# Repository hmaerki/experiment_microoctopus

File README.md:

# HIL (Hardware in the Loop) testinfrastructure

**This repo has to be moved to https://github.com/octoprobe**

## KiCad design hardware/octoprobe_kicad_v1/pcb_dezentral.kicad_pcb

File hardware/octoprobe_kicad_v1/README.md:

# Octoprobe v1

## Terms
`opto-pico`: The raspberry pi pico which controls the tentacle

## Goals to be achieved with this board

### No button update of opto-pico

Setup
* 1 tentacle with opto-pico

Result
* Tune TP6 cap for BOOTSEL-mode

### Automate opto-pico

Setup
* 1 RHS USB Hub (2 opto-pico)
* Two tentacles

Result
* Automatically detect tentacles on USB hub (pyusb, pyudev)
* Automatically update micropython on opto-pico
* Assignments of opto-pico serial to USB hub port identifier

### Update DUT

Setup
* 1 RHS USB Hub (2 opto-pico, 1 DUT-pico, 1 DUT-pyboard)
* Tentacle A: Raspberry Pi Pico
  * update pico using `picotool`
* Tentacle B: pyboard
  * update pybard using `dfu-util`

Result
* Automatically update FW on tentacle A
  * Optorelays on boot button
  * install micropython and testcode
* Automatically update FW on tentacle B
  * Optorelays on boot button
  * install micropython and testcode

## Kicad

### Multiconnector

GND, GND, 3V3, 5V, RELAYS0..5: 10 pins

* Testpoint
* 2 Muffe
* 2 Lötauge

A) Kicad repeat
B) Footprint mit Testpoint, 2 Muffe, 2 Lötauge
C) Footprint mit 10 Testpoint, 10x2 Muffe, 10x2 Lötauge
D) Parametrierbarer Python Code. Symbol Name ist vordefiniert.
E) Symbol `Conn_01x10_Pin`
   Parametrierbarer Python Code, welcher die entsprechenden Pins benennt.

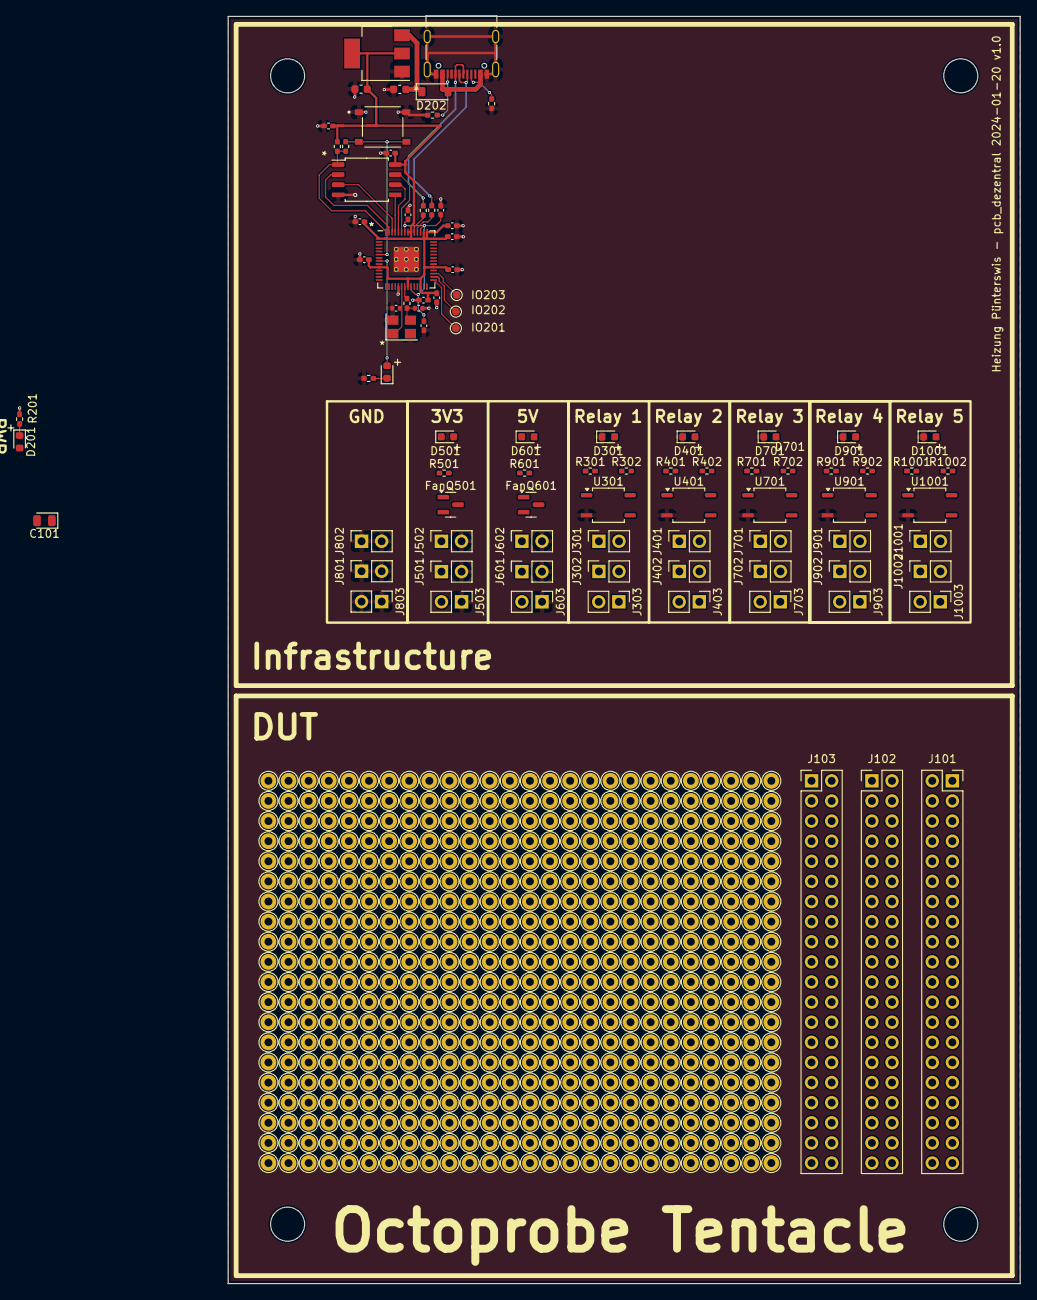
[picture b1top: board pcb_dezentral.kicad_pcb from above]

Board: 2 copper layers, 100.0 x 160.0 mm, 100 parts (0 on the bottom side), 58 nets.

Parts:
C101: 100n 50V; D_0805_2012Metric
C201, C202: 10u; C_0603_1608Metric
C203, C204, C207, C208, C209, C212, C213, C214, C215, C216: 100n; C_0402_1005Metric_Pad0.74x0.62mm_HandSolder
C205, C206: 1u; C_0402_1005Metric_Pad0.74x0.62mm_HandSolder
C210, C211: 30p; C_0402_1005Metric
D101, D301, D401, D701, D901, D1001: LED WHITE; LED_0603_1608Metric
D201: LED GREEN; LED_0603_1608Metric
D202: B5819W SL; D_SOD-123
D501, D601: RED; LED_0603_1608Metric
FanQ501, FanQ601: NMOS; SOT-23
IO201, IO202, IO203: TestPoint; TestPoint_Pad_D1.0mm
J101: Conn_01x20; PinSocket_2x20_P2.54mm_Vertical-stackable
J102: Conn_01x20; PinSocket_2x20_P2.54mm_Vertical-mirrored
J103: Conn_01x20; PinSocket_2x20_P2.54mm_Vertical-mirrored-bare
J201: USB_C_Receptacle_USB2.0; USB_C_Receptacle_Palconn_UTC16-G
J301, J302, J401, J402, J501, J502, J601, J602, J701, J702, J801, J802, J901, J902, J1001, J1002: Conn_01x02_Socket; PinSocket_1x02_P2.54mm_Vertical
J303, J403, J503, J603, J703, J803, J903, J1003: Conn_01x02_Pin; PinHeader_1x02_P2.54mm_Vertical
R101, R201, R501, R601: 470R; R_0402_1005Metric_Pad0.72x0.64mm_HandSolder
R202, R203: 27R; R_0402_1005Metric_Pad0.72x0.64mm_HandSolder
R204, R205: 5.1K; R_0402_1005Metric_Pad0.72x0.64mm_HandSolder
R206: 1K; R_0402_1005Metric_Pad0.72x0.64mm_HandSolder
R207, R302, R402, R702, R902, R1002: 10K; R_0402_1005Metric_Pad0.72x0.64mm_HandSolder
R208, R301, R401, R701, R901, R1001: 1k; R_0402_1005Metric_Pad0.72x0.64mm_HandSolder
SW201: SW_MEC_5E; SW_TS-1187A-B-A-B
U201: RP2040; RP2040-QFN-56
U202: AMS1117-3.3; SOT-223-3_TabPin2
U203: W25Q128JVS; SOIC-8_5.23x5.23mm_P1.27mm
U301, U401, U701, U901, U1001: GAQY221S; SOP-4_3.8x4.1mm_P2.54mm
UR101, UR801: GND; opctoprobe_relay
UR301: Relay 1; opctoprobe_relay
UR401: Relay 2; opctoprobe_relay
UR501: 3V3; opctoprobe_relay
UR601: 5V; opctoprobe_relay
UR701: Relay 3; opctoprobe_relay
UR901: Relay 4; opctoprobe_relay
UR1001: Relay 5; opctoprobe_relay
Y201: Crystal_GND24_Small; Crystal_SMD_3225-4Pin_3.2x2.5mm

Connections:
+1V1: C203.1, C204.1, C205.1, U201.23 (DVDD), U201.45 (VREG-VOUT), U201.50 (DVDD)
+3V3: C101.2, C202.1, C206.1, C207.1, C208.1, C209.1, C212.1, C213.1, C214.1, C215.1, C216.1, D201.2 (A), FanQ501.3 (D), R207.1, U201.1 (IOVDD), U201.10 (IOVDD), U201.22 (IOVDD), U201.26 (RUN), U201.33 (IOVDD), U201.42 (IOVDD), U201.43 (ADC-AVDD), U201.44 (VREG-VIN), U201.48 (USB-VDD), U201.49 (IOVDD), U202.2 (VO), U203.8 (VCC)
+5V: C201.1, D202.1 (K), FanQ601.3 (D), U202.3 (VI)
/Relay 4/RELAY_IN: R901.2, R902.1
/Relay 5/RELAY_IN: R1001.2, R1002.1
/cpu/QSPI_SCLK: U201.52 (QSPI-SCLK), U203.6 (CLK)
/cpu/QSPI_SD0: U201.53 (QSPI-SD0), U203.5 (DI(IO0))
/cpu/QSPI_SD1: U201.55 (QSPI-SD1), U203.2 (DO(IO1))
/cpu/QSPI_SD2: U201.54 (QSPI-SD2), U203.3 (IO2)
/cpu/QSPI_SD3: U201.51 (QSPI-SD3), U203.7 (IO3)
/cpu/QSPI_SS: R206.2, R207.2, U201.56 (QSPI-SS-N), U203.1 (~CS)
/cpu/USB_D+: J201.A6 (D+), J201.B6 (D+), R202.1
/cpu/USB_D-: J201.A7 (D-), J201.B7 (D-), R203.1
/cpu/XIN: C210.1, U201.20 (XIN), Y201.1
/cpu/XOUT: R208.1, U201.21 (XOUT)
DUT_3V3: FanQ501.2 (S), J501.1, J502.1, J503.2, R501.2
DUT_5V: FanQ601.2 (S), J601.1, J602.1, J603.2, R601.2
GND: C101.1, C201.2, C202.2, C203.2, C204.2, C205.2, C206.2, C207.2, C208.2, C209.2, C210.2, C211.2, C212.2, C213.2, C214.2, C215.2, C216.2, D301.1 (K), D401.1 (K), D701.1 (K), D901.1 (K), D1001.1 (K), J201.A1 (GND), J201.A12 (GND), J201.B1 (GND), J201.B12 (GND), J201.S1 (SHIELD), J501.2, J502.2, J503.1, J601.2, J602.2, J603.1, J801.1, J801.2, J802.1, J802.2, J803.1, J803.2, R101.1, R201.1, R204.2, R205.2, SW201.1, SW201.2, U201.19 (TESTEN), U201.57 (GND), U202.1 (GND), U203.4 (GND), U301.2, U401.2, U701.2, U901.2, U1001.2, Y201.2, Y201.4
unnamed: C211.1, R208.2, Y201.3
unnamed: D101.1 (K), R101.2
unnamed: D201.1 (K), R201.2
unnamed: D202.2 (A), J201.A4 (VBUS), J201.A9 (VBUS), J201.B4 (VBUS), J201.B9 (VBUS)
unnamed: D301.2 (A), R301.1
unnamed: D401.2 (A), R401.1
unnamed: D501.2 (A), FanQ501.1 (G)
unnamed: D501.1 (K), R501.1
unnamed: D601.2 (A), FanQ601.1 (G)
unnamed: D601.1 (K), R601.1
unnamed: D701.2 (A), R701.1
unnamed: D901.2 (A), R901.1
unnamed: D1001.2 (A), R1001.1
unnamed: J201.A5 (CC1), R204.1
unnamed: J201.B5 (CC2), R205.1
unnamed: J301.1, J302.1, J303.2, U301.4
unnamed: J301.2, J302.2, J303.1, U301.3
unnamed: J401.1, J402.1, J403.2, U401.4
unnamed: J401.2, J402.2, J403.1, U401.3
unnamed: J701.1, J702.1, J703.2, U701.4
unnamed: J701.2, J702.2, J703.1, U701.3
unnamed: J901.1, J902.1, J903.2, U901.4
unnamed: J901.2, J902.2, J903.1, U901.3
unnamed: J1001.1, J1002.1, J1003.2, U1001.4
unnamed: J1001.2, J1002.2, J1003.1, U1001.3
unnamed: R302.2, U301.1
unnamed: R402.2, U401.1
unnamed: R702.2, U701.1
unnamed: R902.2, U901.1
unnamed: R1002.2, U1001.1
unnamed: IO201.1, U201.29 (GPIO18)
unnamed: IO202.1, U201.30 (GPIO19)
unnamed: IO203.1, U201.31 (GPIO20)
unnamed: R203.2, U201.46 (USB-DM)
unnamed: R202.2, U201.47 (USB-DP)
RELAIS_1: R301.2, R302.1, U201.3 (GPIO1)
RELAIS_2: R401.2, R402.1
RELAIS_3: R701.2, R702.1
ZENTRALE_LED: D101.2 (A), U201.8 (GPIO6)
button: R206.1, SW201.3 (K), SW201.4 (A), U201.6 (GPIO4)

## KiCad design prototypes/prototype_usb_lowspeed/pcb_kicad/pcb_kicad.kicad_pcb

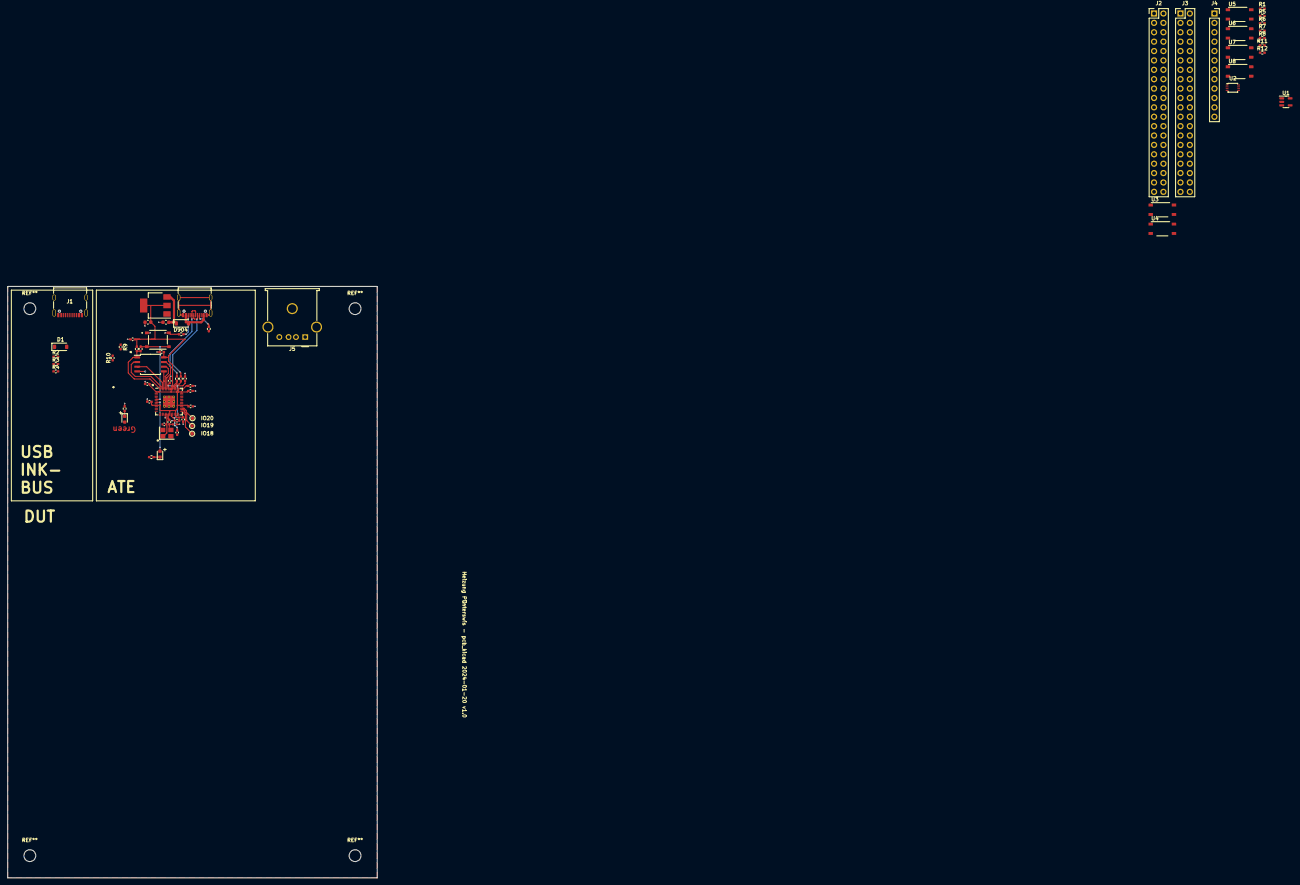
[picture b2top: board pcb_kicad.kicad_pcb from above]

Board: 2 copper layers, 100.0 x 160.0 mm, 63 parts (0 on the bottom side), 51 nets.

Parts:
C901, C902: 10u; C_0603_1608Metric
C903, C904, C907, C908, C911, C912, C913, C914, C915, C916: 100n; C_0402_1005Metric_Pad0.74x0.62mm_HandSolder
C905, C906: 1u; C_0402_1005Metric_Pad0.74x0.62mm_HandSolder
C909, C910: 30p; C_0402_1005Metric
D1, D904: B5819W SL; D_SOD-123
D28: LED WHITE; LED_0603_1608Metric
D901: LED GREEN; LED_0603_1608Metric
IO18, IO19, IO20: TestPoint; TestPoint_Pad_D1.0mm
J1, J901: USB_C_Receptacle_USB2.0; USB_C_Receptacle_Palconn_UTC16-G
J2: Conn_01x20; PinSocket_2x20_P2.54mm_Vertical-mirrored
J3: Conn_01x20; PinSocket_2x20_P2.54mm_Vertical-mirrored-bare
J4: Conn_01x12; PinSocket_1x12_P2.54mm_Vertical
J5: USB_A; USB_A_Molex_67643_Horizontal_with_solder_tab
R1: 100; R_0402_1005Metric_Pad0.72x0.64mm_HandSolder
R2, R3, R901, R902: 5.1K; R_0402_1005Metric_Pad0.72x0.64mm_HandSolder
R4: 10; R_0402_1005Metric_Pad0.72x0.64mm_HandSolder
R5, R6, R7, R8, R9, R10, R11, R12: 0; R_0402_1005Metric_Pad0.72x0.64mm_HandSolder
R20, R905: 470R; R_0402_1005Metric_Pad0.72x0.64mm_HandSolder
R903, R904: 27R; R_0402_1005Metric_Pad0.72x0.64mm_HandSolder
R906: 1K; R_0402_1005Metric_Pad0.72x0.64mm_HandSolder
R907: 10K; R_0402_1005Metric_Pad0.72x0.64mm_HandSolder
R908: 1k; R_0402_1005Metric_Pad0.72x0.64mm_HandSolder
SW901: SW_MEC_5E; SW_TS-1187A-B-A-B
U1: LPW5209B5F-21; SOT-23-5
U2: FSUSB31K8X; VSSOP-8_2.4x2.1mm_P0.5mm
U3, U4, U5, U6, U7, U8: TLP172GM; MFSOP6-4_4.4x3.6mm_P1.27mm
U901: RP2040; RP2040-QFN-56
U902: AMS1117-3.3; SOT-223-3_TabPin2
U903: W25Q128JVS; SOIC-8_5.23x5.23mm_P1.27mm
Y901: Crystal_GND24_Small; Crystal_SMD_3225-4Pin_3.2x2.5mm

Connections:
+1V1: C903.1, C904.1, C905.1, U901.23 (DVDD), U901.45 (VREG-VOUT), U901.50 (DVDD)
+3V3: C902.1, C906.1, C907.1, C908.1, C911.1, C912.1, C913.1, C914.1, C915.1, C916.1, D901.2 (A), J4.3, R1.1, R4.2, R907.1, U901.1 (IOVDD), U901.10 (IOVDD), U901.22 (IOVDD), U901.26 (RUN), U901.33 (IOVDD), U901.42 (IOVDD), U901.43 (ADC-AVDD), U901.44 (VREG-VIN), U901.48 (USB-VDD), U901.49 (IOVDD), U902.2 (VO), U903.8 (VCC)
+5V: C901.1, D904.1 (K), J4.4, U902.3 (VI)
/cpu/QSPI_SCLK: U901.52 (QSPI-SCLK), U903.6 (CLK)
/cpu/QSPI_SD0: U901.53 (QSPI-SD0), U903.5 (DI(IO0))
/cpu/QSPI_SD1: U901.55 (QSPI-SD1), U903.2 (DO(IO1))
/cpu/QSPI_SD2: U901.54 (QSPI-SD2), U903.3 (IO2)
/cpu/QSPI_SD3: U901.51 (QSPI-SD3), U903.7 (IO3)
/cpu/QSPI_SS: R906.2, R907.2, U901.56 (QSPI-SS-N), U903.1 (~CS)
/cpu/USB_D+: J901.A6 (D+), J901.B6 (D+), R903.1
/cpu/USB_D-: J901.A7 (D-), J901.B7 (D-), R904.1
/cpu/XIN: C909.1, U901.20 (XIN), Y901.1
/cpu/XOUT: R908.1, U901.21 (XOUT)
DUT_ENABLE_USB2: U5.1, U6.1
DUT_GND: C901.2, C902.2, C903.2, C904.2, C905.2, C906.2, C907.2, C908.2, C909.2, C910.2, C911.2, C912.2, C913.2, C914.2, C915.2, C916.2, J1.A1 (GND), J1.A12 (GND), J1.B1 (GND), J1.B12 (GND), J1.S1 (SHIELD), J2.1, J4.1, J4.2, J5.4 (GND), J5.5 (Shield), J901.A1 (GND), J901.A12 (GND), J901.B1 (GND), J901.B12 (GND), J901.S1 (SHIELD), R2.2, R3.2, R20.1, R901.2, R902.2, R905.1, SW901.1, SW901.2, U1.2 (GND), U2.4 (GND), U5.3, U6.3, U7.3, U8.3, U901.19 (TESTEN), U901.57 (GND), U902.1 (GND), U903.4 (GND), Y901.2, Y901.4
DUT_USB_D+: J4.11, R8.1, R12.1
DUT_USB_D-: J4.12, R7.1, R10.1
IB_USB_DUT_5V: D1.1 (K), J2.5, J5.1 (VBUS), U1.5 (IN)
IB_USB_DUT_D+: J2.11, J5.3 (D+), R6.2, R11.1
IB_USB_DUT_D-: J2.9, J5.2 (D-), R5.2, R9.1
unnamed: C910.1, R908.2, Y901.3
unnamed: D1.2 (A), J1.A4 (VBUS), J1.A9 (VBUS), J1.B4 (VBUS), J1.B9 (VBUS)
unnamed: D28.1 (K), R20.2
unnamed: D901.1 (K), R905.2
unnamed: D904.2 (A), J901.A4 (VBUS), J901.A9 (VBUS), J901.B4 (VBUS), J901.B9 (VBUS)
unnamed: J1.A5 (CC1), R2.1
unnamed: J1.B5 (CC2), R3.1
unnamed: J901.A5 (CC1), R901.1
unnamed: J901.B5 (CC2), R902.1
unnamed: J1.A7 (D-), J1.B7 (D-), R4.1
unnamed: J1.A6 (D+), J1.B6 (D+)
unnamed: R9.2, U5.6
unnamed: R10.2, U5.4
unnamed: R11.2, U6.6
unnamed: R12.2, U6.4
unnamed: R6.1, U2.5 (D+)
unnamed: R5.1, U2.3 (D-)
unnamed: R8.2, U2.6 (HSD+)
unnamed: R7.2, U2.2 (HSD-)
unnamed: R1.2, U2.8 (VCC)
unnamed: IO18.1, U901.29 (GPIO18)
unnamed: IO19.1, U901.30 (GPIO19)
unnamed: IO20.1, U901.31 (GPIO20)
unnamed: R904.2, U901.46 (USB-DM)
unnamed: R903.2, U901.47 (USB-DP)
SW1a (Boot): J4.7, U7.6
SW1b (Boot): J4.8, U7.4
SW2a: J4.9, U8.6
SW2b: J4.10, U8.4
ZENTRALE_LED: D28.2 (A), U901.8 (GPIO6)
button: R906.1, SW901.3 (K), SW901.4 (A), U901.6 (GPIO4)

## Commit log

2024-01-12 Initial ideas
2024-01-13 Initial ideas 2
2024-01-13 Add collected_shields
2024-01-13 RPi_Hat
2024-01-14 RPi_Hat 2
2024-01-14 Some documentation
2024-01-17 uOctopus -> microOctopus
2024-01-17 readme to clone kicad parts repos
2024-02-26 Add usb hubs
2024-02-26 New pcb_experiment_usb10
2024-04-01 bootsel / pysub / pyudev
2024-04-01 microprobe_kicad_v1: Import from heizung_2023
2024-04-01 microprobe -> octoprobe
2024-05-06 Add some RSH hubs
2024-05-06 Moved many documents to pyhubctl
2024-05-06 cleanup pcb
2024-05-06 initial
2024-05-06 rename
2024-05-06 update sheet names
2024-05-06 Relay
2024-05-06 Breakout Board
2024-05-06 Mounting
2024-06-23 PCB octoprobe tentacle v1.0
2024-06-23 Feedback for v0.0.1
2024-06-23 v1 rc1
2024-06-23 Initial implementation of octoprobe
2024-06-23 octoprobe_logo
2024-06-23 Improve PCB
2024-06-23 Add 5V 500mA
2024-06-23 Cable Tie
2024-06-23 octoprobe_logo_v3
2024-06-23 Works mit RSH-A10
2024-06-26 Cleanup typehints. Automate static checking.
2024-06-30 Initial workflow
2024-06-30 Initial gitlab workflow
2024-07-03 Implementation of SW for tentacle v0.3 started
2024-07-13 tentacle v0.2 ordered at JLCPCB
2024-07-13 Implemented 'op query'
2024-07-16 tentacle v0.2: readme_errors_v0.2.md
2024-07-16 infrastructure_tutorial
2024-07-16 Cleanup images
2024-07-19 Bolzone
2024-08-04 GPIO09
2024-08-04 Connect pyboard/pico to ground
2024-08-04 pytest proove of concept
2024-08-05 pytest for infrastructure_tutorial
2024-08-05 PCB: Move RP2
2024-08-05 octoprobe_kicad_v0.3
2024-08-05 PCB: Version number
2024-08-05 PCB: Production files ready
2024-08-05 PCB: Octobus
2024-08-05 PCB: Add "Open Hardware"
2024-08-05 PCB: Oscillator
2024-08-05 pytest: Introduce --firmware
2024-08-06 Refactored lib_tentacle.py
2024-08-06 Fixed 'pip install .'
2024-08-13 New: Tentacle Parts List
2024-08-13 New: assessment_sigrok
2024-08-13 New: 'op commissioning'
2024-08-16 Update documentation
2024-08-18 convert_svg_2_png.sh
2024-08-18 Deleted directories which have been moved to github/octoprobe

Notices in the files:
hardware/octoprobe_kicad_v1/pcb_dezentral.kicad_pcb:
Released under MIT Open-source License
parts and their libraries:
License: CC BY 4.0
